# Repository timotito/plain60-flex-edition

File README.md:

# Plain60 Flex Edition rev2.2.1
This is an independently developed branch of the Plain60 Flex Edition, by evyd13.

This universal 60% PCB is designed to support as little layouts as possible without limiting usability for most users. The reason evyd13 did this is because other PCBs made for this form factor usually have so many supported layouts that it could almost qualify as swiss cheese.

It also features a fuse and an ESD protection chip to protect the MCU and other parts of the PCB.

## Features
- Fits in the TGR Unikorn
- Compatible with QMK Firmware and VIA Configurator (if you flash a VIA compatible .hex file)
- Compatible with most universal 60% cases and HHKB/WKL Tofu by KBDfans
- USB type-C
- Optional JST header for connection with daughterboard
- Footprint for optional speaker (AST1109MLTRQ)
- ESD protection and fuse
- No LEDs and no underglow
- Minimal layout support
- ISP header

## Supported layouts

## Building
If you feel like building a few of these PCBs yourself, the required gerber files are in the named folder. Order those at your favourite PCB manufacturer, get the components needed (see included BOM) and solder them on! Alternatively, request SMT assembly from the manufacturer.

A hot air station is not required but a soldering iron is. Flux is recommended.

## Opening the project
To open the files you will need KiCAD.

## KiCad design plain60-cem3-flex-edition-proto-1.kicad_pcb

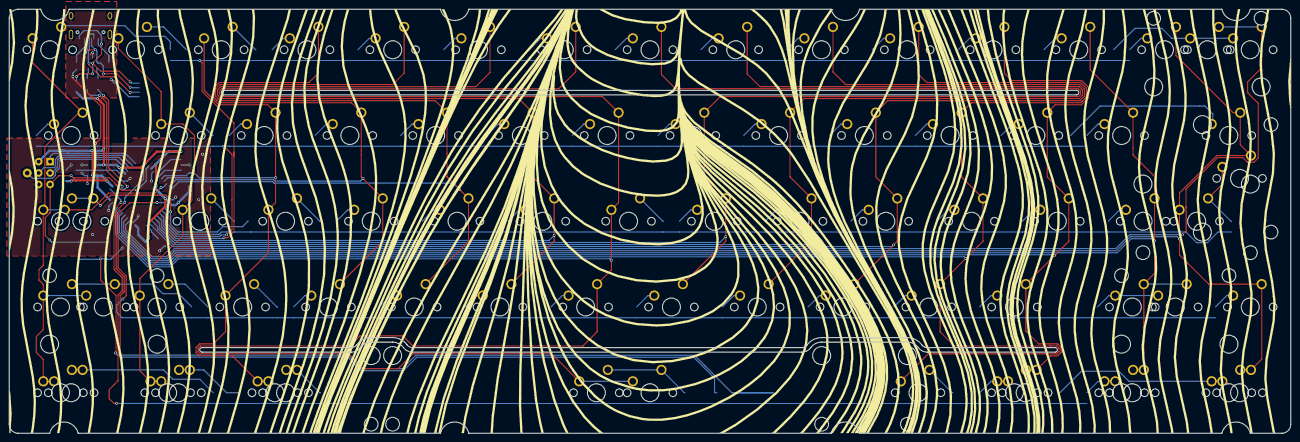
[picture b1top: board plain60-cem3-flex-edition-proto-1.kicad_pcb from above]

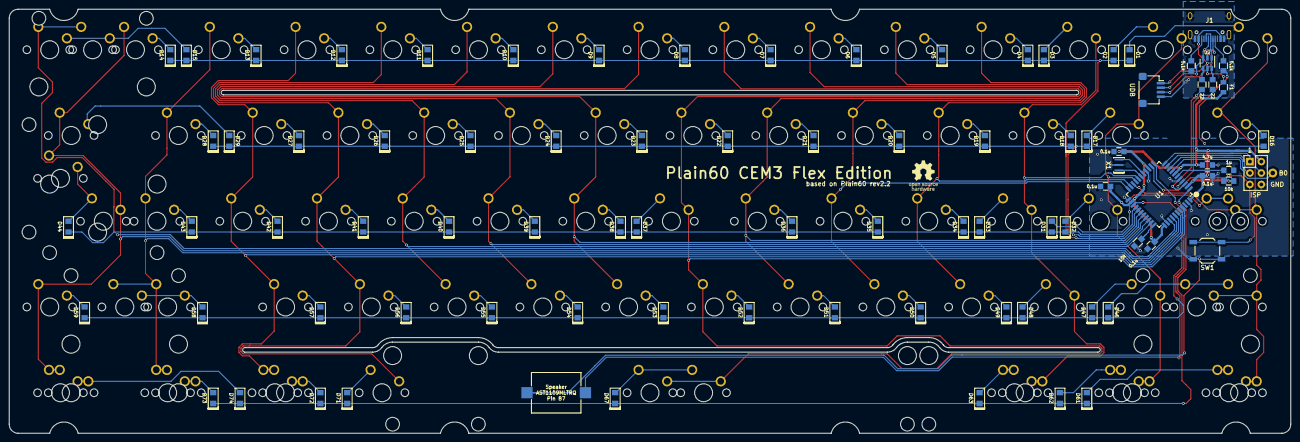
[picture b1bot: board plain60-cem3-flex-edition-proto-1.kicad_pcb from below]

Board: 2 copper layers, 284.7 x 94.2 mm, 174 parts (87 on the bottom side), 106 nets.

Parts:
C1: 1u; C_0805
C2, C3, C4, C5: 0.1u; C_0805
C6: 4.7u; C_0805
D1: D1; D_0805
D2: D2; D_0805
D3: D3; D_0805
D4: D4; D_0805
D5: D5; D_0805
D6: D6; D_0805
D7: D7; D_0805
D8: D8; D_0805
D9: D9; D_0805
D10: D10; D_0805
D11: D11; D_0805
D12: D12; D_0805
D13: D13; D_0805
D14: D14; D_0805
D15: D15; D_0805
D16: D16; D_0805
D17: D17; D_0805
D18: D18; D_0805
D19: D19; D_0805
D20: D20; D_0805
D21: D21; D_0805
D22: D22; D_0805
D23: D23; D_0805
D24: D24; D_0805
D25: D25; D_0805
D26: D26; D_0805
D27: D27; D_0805
D28: D28; D_0805
D29: D29; D_0805
D31: D31; D_0805
D32: D32; D_0805
D33: D33; D_0805
D34: D34; D_0805
D35: D35; D_0805
D36: D36; D_0805
D37: D37; D_0805
D38: D38; D_0805
D39: D39; D_0805
D40: D40; D_0805
D41: D41; D_0805
D42: D42; D_0805
D43: D43; D_0805
D44: D44; D_0805
D46: D46; D_0805
D47: D47; D_0805
D48: D48; D_0805
D49: D49; D_0805
D50: D50; D_0805
D51: D51; D_0805
D52: D52; D_0805
D53: D53; D_0805
D54: D54; D_0805
D55: D55; D_0805
D56: D56; D_0805
D57: D57; D_0805
D58: D58; D_0805
D59: D59; D_0805
D61: D61; D_0805
D62: D62; D_0805
D63: D63; D_0805
D67: D67; D_0805
D71: D71; D_0805
D72: D72; D_0805
D73: D73; D_0805
D74: D74; D_0805
F1: Polyfuse; R_0805
H1: B0; free_pin
J1: HRO-TYPE-C-31-M-12
J2: ISP; isp_standard
J3: ai03_ud; JST_SH_SM04B-SRSS-TB_1x04-1MP_P1.00mm_Horizontal
K1, K2, K3, K4, K5, K6, K7, K8, K9, K10, K11, K12, K13, K14, K15-1, K17, K18, K19, K20, K21, K22, K23, K24, K25, K26, K27, K28, K32, K33, K34, K35, K36, K37, K38, K39, K40, K41, K42, K43, K47, K48, K49, K50, K51, K52, K53, K54, K55, K56, K57, K59, K62-1, K73-1: KEYSW; CHERRY_PLATE_100H
K15: KEYSW; CHERRY_PCB_200H
K16, K29, K61-1, K63-1, K72-1, K74-1: KEYSW; CHERRY_PLATE_150H
K31, K58-1: KEYSW; CHERRY_PLATE_175H
K31-1, K46-1, K61, K62, K63, K71, K72, K73, K74: KEYSW; CHERRY_PLATE_125H
K44: KEYSW; CHERRY_PCB_225H_F
K44-1: KEYSW; CHERRY_PCB_200H_V
K46: KEYSW; CHERRY_PCB_225H
K58: KEYSW; CHERRY_PCB_275H
K67: KEYSW; CHERRY_PCB_625H_F
K67-1: KEYSW; CHERRY_PCB_700H_F
LS1: Speaker; speaker_AST1109MLTRQ
R1, R2: 22; R_0805
R3, R4: 5.1k; R_0805
R5, R6: 10k; R_0805
Ref**: Val**; redss
S1, S2, S3, S6: Screw; 5.5_5x2.5mm
S4, S5: Screw; 10x5_7x2.5mm
S7, S8, S9: Tofu screw; 5.5_5x2.5mm
SW1: SW_PUSH; SW_SPST_TL3342
U1: ATmega32U4; ATMEGA32U4
U2: USBLC6-2SC6
X1: XTAL_GND; Resonator_SMD_muRata_CSTNExxV-3Pin-p1.2

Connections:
D+: J1.6 (DP1), J1.8 (DP2), J3.3, U2.1 (I/O1)
D-: J1.5 (DN2), J1.7 (DN1), J3.2, U2.3 (I/O2)
GND: C1.2, C2.1, C3.1, C4.1, C5.1, C6.1, J1.1 (GND), J1.12 (GND), J1.13 (SHIELD), J2.6, J3.4, LS1.2, R3.1, R4.2, R6.1, SW1.1, U1.5 (UGND), U1.15 (GND), U1.23 (GND), U1.35 (GND), U1.43 (GND), U2.2 (GND), X1.3
MISO: J2.1, U1.11 ((PDO/MISO/PCINT3)PB3)
MOSI: J2.4, U1.10 ((PDI/MOSI/PCINT2)PB2)
unnamed: C1.1, U1.6 (UCAP)
unnamed: D1.2 (A), K1.1
unnamed: D2.2 (A), K2.1
unnamed: D3.2 (A), K3.1
unnamed: D4.2 (A), K4.2
unnamed: D5.2 (A), K5.2
unnamed: D6.2 (A), K6.2
unnamed: D7.2 (A), K7.2
unnamed: D8.2 (A), K8.2
unnamed: D9.2 (A), K9.2
unnamed: D10.2 (A), K10.2
unnamed: D11.2 (A), K11.2
unnamed: D12.2 (A), K12.2
unnamed: D13.2 (A), K13.2
unnamed: D14.2 (A), K14.2
unnamed: D15.2 (A), K15.2, K15-1.2
unnamed: D16.2 (A), K16.2
unnamed: D17.2 (A), K17.1
unnamed: D18.2 (A), K18.2
unnamed: D19.2 (A), K19.2
unnamed: D20.2 (A), K20.2
unnamed: D21.2 (A), K21.2
unnamed: D22.2 (A), K22.2
unnamed: D23.2 (A), K23.2
unnamed: D24.2 (A), K24.2
unnamed: D25.2 (A), K25.2
unnamed: D26.2 (A), K26.2
unnamed: D27.2 (A), K27.2
unnamed: D28.2 (A), K28.2
unnamed: D29.2 (A), K29.2
unnamed: D31.2 (A), K31.1, K31-1.1
unnamed: D32.2 (A), K32.1
unnamed: D33.2 (A), K33.1
unnamed: D34.2 (A), K34.2
unnamed: D35.2 (A), K35.2
unnamed: D36.2 (A), K36.2
unnamed: D37.2 (A), K37.1
unnamed: D38.2 (A), K38.2
unnamed: D39.2 (A), K39.2
unnamed: D40.2 (A), K40.2
unnamed: D41.2 (A), K41.2
unnamed: D42.2 (A), K42.2
unnamed: D43.2 (A), K43.2
unnamed: D44.2 (A), K44.1, K44-1.2
unnamed: D46.2 (A), K46.1, K46-1.1
unnamed: D47.2 (A), K47.1
unnamed: D48.2 (A), K48.1
unnamed: D49.2 (A), K49.2
unnamed: D50.2 (A), K50.2
unnamed: D51.2 (A), K51.2
unnamed: D52.2 (A), K52.2
unnamed: D53.2 (A), K53.2
unnamed: D54.2 (A), K54.2
unnamed: D55.2 (A), K55.2
unnamed: D56.2 (A), K56.2
unnamed: D57.2 (A), K57.2
unnamed: D58.2 (A), K58.2, K58-1.2
unnamed: D59.2 (A), K59.2
unnamed: D61.2 (A), K61.1, K61-1.1
unnamed: D62.2 (A), K62.1, K62-1.1
unnamed: D63.2 (A), K63.1, K63-1.1
unnamed: D67.2 (A), K67.1, K67-1.1
unnamed: D71.2 (A), K71.1
unnamed: D72.2 (A), K72.2, K72-1.2
unnamed: D73.2 (A), K73.2, K73-1.2
unnamed: D74.2 (A), K74.2, K74-1.2
unnamed: H1.1, U1.8 ((SS/PCINT0)PB0)
unnamed: J1.4 (CC1), R3.2
unnamed: J1.10 (CC2), R4.1
unnamed: LS1.1, U1.12 ((OC0A/OC1C/~RTS~/PCINT7)PB7)
unnamed: R1.1, U1.4 (D+)
unnamed: R1.2, U2.6 (I/O1)
unnamed: R2.1, U2.4 (I/O2)
unnamed: R2.2, U1.3 (D-)
unnamed: R6.2, U1.33 ((~HWB~)PE2)
unnamed: U1.16 (XTAL2), X1.2
unnamed: U1.17 (XTAL1), X1.1
RST: J2.5, R5.1, SW1.2, U1.13 (RESET)
SCK: J2.3, U1.9 ((SCLK/PCINT1)PB1)
VBUS: F1.2, J1.2 (VBUS), J1.11 (VBUS), J3.1, U2.5 (VBUS)
VCC: C2.2, C3.2, C4.2, C5.2, C6.2, F1.1, J2.2, R5.2, U1.2 (UVCC), U1.7 (VBUS), U1.14 (VCC), U1.24 (AVCC), U1.34 (VCC), U1.44 (AVCC)
col0: K1.2, K16.1, K31.2, K31-1.2, K46.2, K46-1.2, K61.2, K61-1.2, U1.20 ((RXD/INT2)PD2)
col1: K2.2, K17.2, K32.2, K47.2, K62.2, K62-1.2, U1.19 ((SDA/INT1)PD1)
col2: K3.2, K18.1, K33.2, K48.2, K63.2, K63-1.2, U1.18 ((OC0B/SCL/INT0)PD0)
col3: K4.1, K19.1, K34.1, K49.1, U1.21 ((TXD/INT3)PD3)
col4: K5.1, K20.1, K35.1, K50.1, U1.22 ((XCK1/~CTS~)PD5)
col5: K6.1, K21.1, K36.1, K51.1, U1.29 ((ADC12/OC1A/~OC4B~/PCINT12)PB5)
col6: K7.1, K22.1, K37.2, K52.1, K67.2, K67-1.2, U1.41 ((ADC0)PF0)
col7: K8.1, K23.1, K38.1, K53.1, U1.30 ((ADC13/OC1B/OC4B/PCINT13)PB6)
col8: K9.1, K24.1, K39.1, K54.1, U1.31 ((OC3A/~OC4A~)PC6)
col9: K10.1, K25.1, K40.1, K55.1, U1.32 ((ICP3/CLK0/OC4A)PC7)
col10: K11.1, K26.1, K41.1, K56.1, K71.2, U1.40 ((ADC1)PF1)
col11: K12.1, K27.1, K42.1, K57.1, K72.1, K72-1.1, U1.39 ((ADC4/TCK)PF4)
col12: K13.1, K28.1, K43.1, K58.1, K58-1.1, K73.1, K73-1.1, U1.38 ((ADC5/TMS)PF5)
col13: K14.1, K29.1, K44.2, K44-1.1, K59.1, K74.1, K74-1.1, U1.37 ((ADC6/TDO)PF6)
col14: K15.1, K15-1.1, U1.36 ((ADC7/TDI)PF7)
row0: D1.1 (K), D2.1 (K), D3.1 (K), D4.1 (K), D5.1 (K), D6.1 (K), D7.1 (K), D8.1 (K), D9.1 (K), D10.1 (K), D11.1 (K), D12.1 (K), D13.1 (K), D14.1 (K), D15.1 (K), U1.28 ((ADC11/PCINT4)PB4)
row1: D16.1 (K), D17.1 (K), D18.1 (K), D19.1 (K), D20.1 (K), D21.1 (K), D22.1 (K), D23.1 (K), D24.1 (K), D25.1 (K), D26.1 (K), D27.1 (K), D28.1 (K), D29.1 (K), U1.27 ((T0/OC4D/ADC10)PD7)
row2: D31.1 (K), D32.1 (K), D33.1 (K), D34.1 (K), D35.1 (K), D36.1 (K), D37.1 (K), D38.1 (K), D39.1 (K), D40.1 (K), D41.1 (K), D42.1 (K), D43.1 (K), D44.1 (K), U1.26 ((T1/~OC4D~/ADC9)PD6)
row3: D46.1 (K), D47.1 (K), D48.1 (K), D49.1 (K), D50.1 (K), D51.1 (K), D52.1 (K), D53.1 (K), D54.1 (K), D55.1 (K), D56.1 (K), D57.1 (K), D58.1 (K), D59.1 (K), U1.25 ((ICP2/ADC8)PD4)
row4: D61.1 (K), D62.1 (K), D63.1 (K), D67.1 (K), D71.1 (K), D72.1 (K), D73.1 (K), D74.1 (K), U1.1 ((INT6/AIN0)PE6)

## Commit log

2022-01-24 Modified Plain60
    Added and modified positioning of silkscreen elements for ease of SMT assembly.
    Modified BOM to reduce ambiguity when using silkscreen designators in conjuction with BOM sheet. Also, changed parts list.
